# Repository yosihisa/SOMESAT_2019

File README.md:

# SOMESAT 種コン2019

## これはなに
SOMESAT種コン2019関係のプロジェクトを管理するリポジトリです。  
各CanSatの基板データとかプログラムとかいろいろ  
<br>
<font color="Red">注意: ESFF(仮称)はこのリポジトリではありません。</font>

## 編集するときは？  
自分のブランチを作ってそこにpushしてください。  
その後masterにプルリク送ってください。  
**masterを直接書き換えないでください。**   

## 何があるの？
ディレクトリ構成は以下の通り  

- PCB  
基板データ関係
    - EDAMAME_S  
    えだまめSの基板データ  
    n_yosihisa

    - EDAMAME_WiFimodule  
    ZUNDA～えだまめ!!に使われていたESP8266無線モジュールの基板データ  
    yuuitirou528  

    -  	EDAMAMEv2  
    画像認識機の基板データ  
    n_yosihisa  

- firmware  
プログラム関係  
    - EDAMAME_S  
    環境  
    ・ Arduino IDE  
    ・ ESP32  
    えだまめSのスケッチ  
    n_yosihisa

    - EDAMAME_WiFimodule  
    環境  
    ・ Arduino IDE  
    ・ ESP8266  
    ZUNDA～えだまめ!!に使われていたESP8266無線モジュールのスケッチ  
    yuuitirou528  

    -  EDAMAMEv2  
    環境  
    ・C(HAL)  
    ・Atollic TrueSTUDIO  
    ・CubeMX  
    ・STM32F446   
    画像認識機のプログラム  
    n_yosihisa  

- documents  
文書関係  
仕様書など  

### ファイルを書き替えるときの注意  
基本的に自分の担当しているもののディレクトの中身以外は変更しないように (2018/10/5)
***

## 著作権などについて
基本的に著作権は各作者に帰属します。  
種コンが終わるまで自分が書いたもの以外原則公開禁止です。  
ただし、種コン終了後、このリポジトリをpublicにする可能性があります。

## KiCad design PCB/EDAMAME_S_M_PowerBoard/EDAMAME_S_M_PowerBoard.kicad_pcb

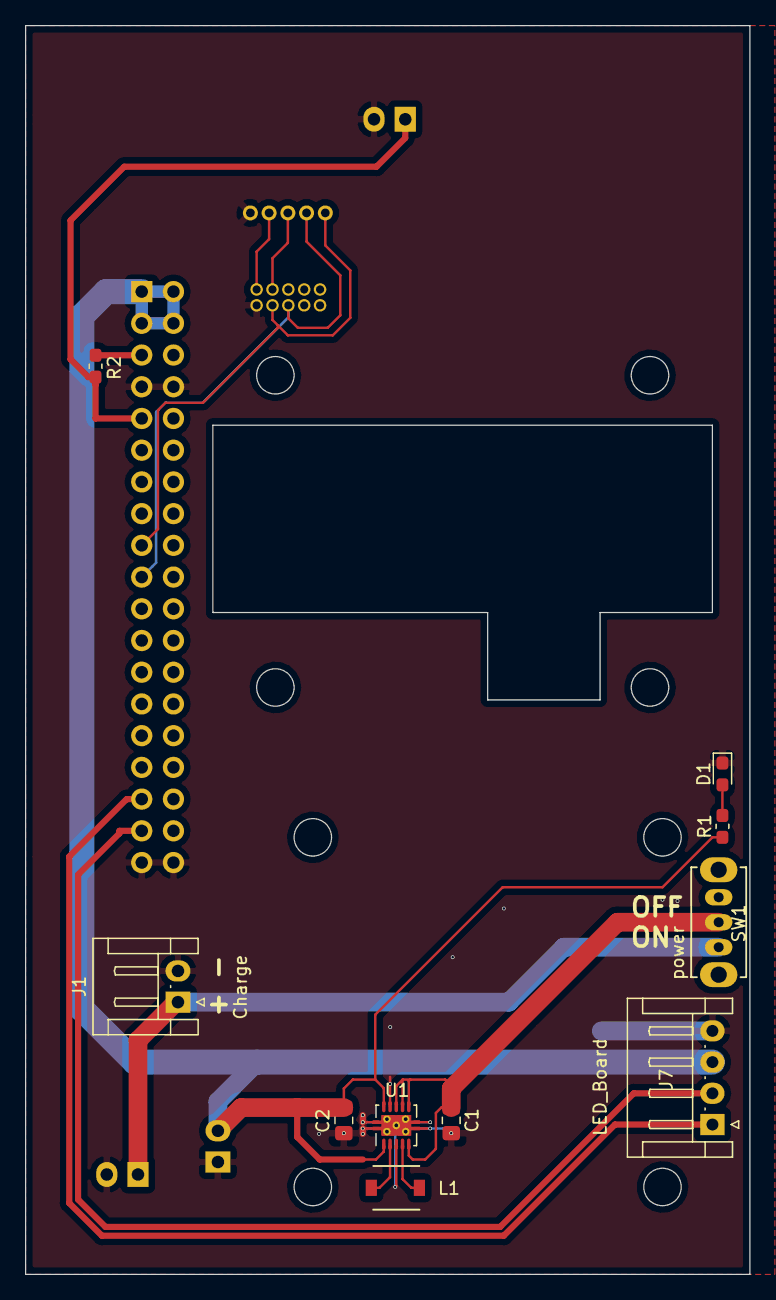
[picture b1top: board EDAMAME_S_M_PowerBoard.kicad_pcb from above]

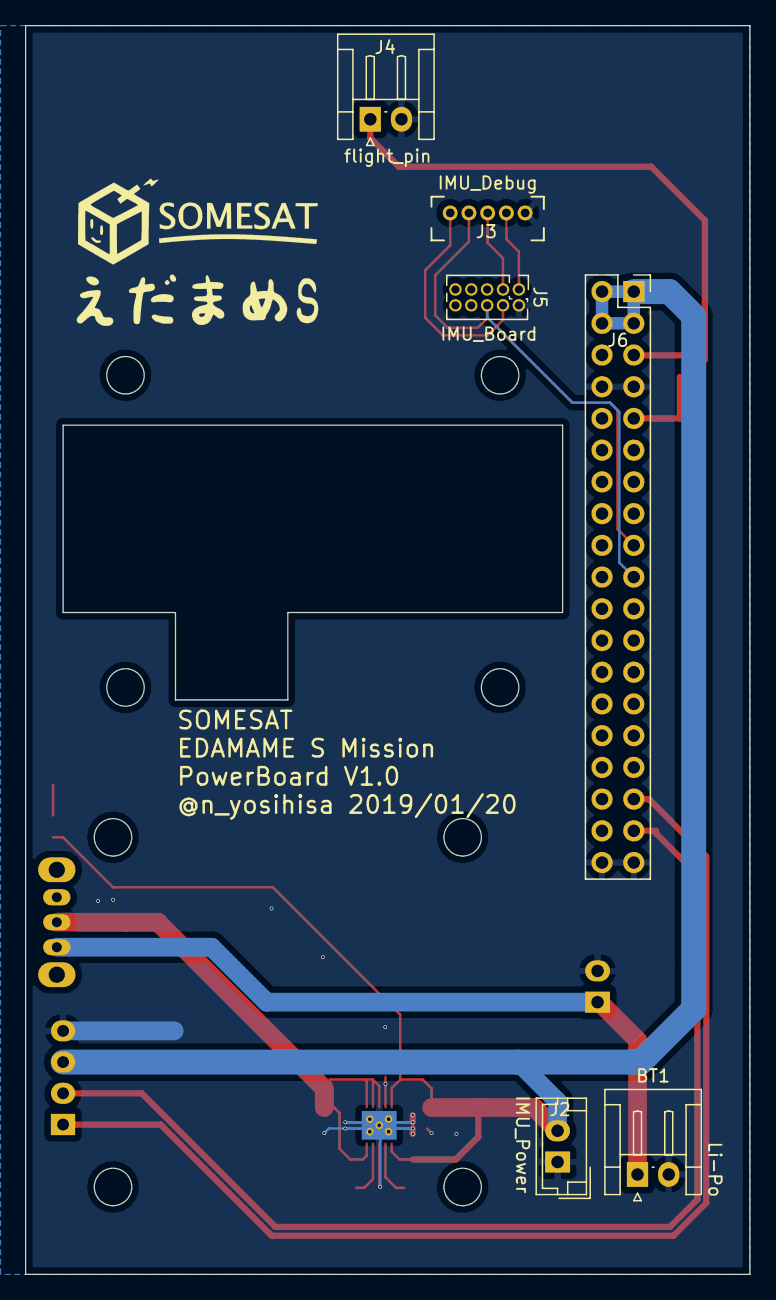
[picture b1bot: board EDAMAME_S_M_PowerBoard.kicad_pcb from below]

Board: 2 copper layers, 58.0 x 100.0 mm, 16 parts (6 on the bottom side), 15 nets.

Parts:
BT1: Li-Po; JST_EH_S02B-EH_1x02_P2.50mm_Horizontal
C1, C2: 10u; C_0805_2012Metric_Pad1.15x1.40mm_HandSolder
D1: LED_Small; LED_0603_1608Metric_Pad1.05x0.95mm_HandSolder
J1: Charge; JST_EH_S02B-EH_1x02_P2.50mm_Horizontal
J2: IMU_Power; JST_EH_B02B-EH-A_1x02_P2.50mm_Vertical
J3: IMU_Debug; STlink
J4: flight_pin; JST_EH_S02B-EH_1x02_P2.50mm_Horizontal
J5: IMU_Board; PinHeader_2x05_P1.27mm_Vertical
J6: OBC_Board; PinSocket_2x19_P2.54mm_Vertical
J7: LED_Board; JST_EH_S04B-EH_1x04_P2.50mm_Horizontal
L1: 2.2uH; inductor_VLF4012-2R2
R1, R2: R; R_0603_1608Metric_Pad1.05x0.95mm_HandSolder
SW1: power; SS-12D01-VG4
U1: TPS63002; Texas_S-PVSON-N10_ThermalVias

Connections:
+3V3: J6.5, R2.2
+5V: C2.1, J2.2, J6.1, J6.2, J6.3, J6.4, J7.3, R1.1, U1.1, U1.10
+BATT: C1.1, SW1.2, U1.5, U1.6, U1.7, U1.8
/IMU_RX: J3.2, J5.6, J6.19
/IMU_TX: J3.1, J5.4, J6.17
/SCL: J6.33, J7.1
/SDA: J6.35, J7.2
/SWCLK: J3.3, J5.3
/SWDIO: J3.4, J5.1
/flight_pin: J4.1, J6.9, R2.1
GND: BT1.2, C1.2, C2.2, D1.1, J1.2, J2.1, J3.5, J4.2, J5.2, J6.7, J6.8, J6.37, J6.38, J7.4, U1.3, U1.9, U1.11
unnamed: BT1.1, J1.1, SW1.1
unnamed: D1.2, R1.2
unnamed: L1.1, U1.4
unnamed: L1.2, U1.2

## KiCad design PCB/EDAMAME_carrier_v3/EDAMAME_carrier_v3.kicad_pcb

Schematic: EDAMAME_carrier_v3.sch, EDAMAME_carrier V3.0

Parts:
BT1, BT2: Li-Po; JST_EH_S02B-EH_1x02_P2.50mm_Horizontal
BZ1: Buzzer; CP_Radial_Tantal_D10.5mm_P5.00mm
C1, C2: 0.1u; C_0603_1608Metric_Pad1.05x0.95mm_HandSolder
C3: 10u; C_0805_2012Metric_Pad1.15x1.40mm_HandSolder
D1, D2, D3: LED_Small; LED_0603_1608Metric_Pad1.05x0.95mm_HandSolder
J1: Charge; JST_EH_B03B-EH-A_1x03_P2.50mm_Vertical
J2: Debug; STlink
J3: flightpin; JST_EH_S02B-EH_1x02_P2.50mm_Horizontal
J4: Nichrome1; JST_EH_S02B-EH_1x02_P2.50mm_Horizontal
J5: Nichrome2; JST_EH_S02B-EH_1x02_P2.50mm_Horizontal
J6: Nichrome3; JST_EH_S02B-EH_1x02_P2.50mm_Horizontal
J7: Nichrome4; JST_EH_S02B-EH_1x02_P2.50mm_Horizontal
Q1, Q2: NDS9936; SO-8_5.3x6.2mm_P1.27mm
R1, R2, R3, R4, R5, R6, R7: 1k; R_0603_1608Metric_Pad1.05x0.95mm_HandSolder
SW1: power; SS-12D01-VG4
SW2, SW3: Delay_0; DIP-10_W7.62mm_LongPads
U1: STM32F042F6Px; TSSOP-20_4.4x6.5mm_P0.65mm
U2: NJM2391DL1-33; TO-252-2

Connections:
+3V3: C1.1, C3.1, R1.1, R3.1, U1.5, U1.16, U2.3 (VO)
+BATT: C2.1, J4.2, J5.2, J6.2, J7.2, SW1.2, U2.1 (VI)
/Buzzer: R2.1, U1.14
/Delay0_0.5s: SW3.4, U1.9
/Delay0_0.25s: SW3.5, U1.10
/Delay0_1s: SW3.3, U1.8
/Delay0_2s: SW3.2, U1.7
/Delay0_4s: SW3.1, U1.6
/Delay1_0.5s: SW2.6, U1.11
/Delay1_1s: SW2.7, U1.12
/Delay1_2s: SW2.8, U1.13
/Delay2_0.5s: SW2.9, U1.3
/Delay2_1s: SW2.10, U1.2
/Flight_SW: J3.1, R3.2, U1.1
/PWM0: Q1.2, Q1.4, R4.1, R6.1, U1.17
/PWM1: Q2.2, Q2.4, R5.1, R7.1, U1.18
/SWCLK: J2.3, U1.19
/SWDIO: J2.4, U1.20
GND: BT2.2, BZ1.2, C1.2, C2.2, C3.2, D1.1, D2.1, D3.1, J1.3, J2.5, J3.2, Q1.1, Q1.3, Q2.1, Q2.3, R6.2, R7.2, SW2.1, SW2.2, SW2.3, SW2.4, SW2.5, SW3.6, SW3.7, SW3.8, SW3.9, SW3.10, U1.15, U2.2 (GND)
unnamed: BT1.1, J1.1, SW1.1
unnamed: BT1.2, BT2.1, J1.2
unnamed: BZ1.1, R2.2
unnamed: D1.2, R1.2
unnamed: D2.2, R4.2
unnamed: D3.2, R5.2
unnamed: J4.1, Q1.7, Q1.8
unnamed: J5.1, Q1.5, Q1.6
unnamed: J6.1, Q2.7, Q2.8
unnamed: J7.1, Q2.5, Q2.6

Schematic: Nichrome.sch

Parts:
D101, D102, D103, D104: LED_Small; LED_0603_1608Metric_Pad1.05x0.95mm_HandSolder
J101: Nichrome1; JST_EH_S02B-EH_1x02_P2.50mm_Horizontal
J102: Nichrome2; JST_EH_S02B-EH_1x02_P2.50mm_Horizontal
J103: Nichrome3; JST_EH_S02B-EH_1x02_P2.50mm_Horizontal
J104: Nichrome4; JST_EH_S02B-EH_1x02_P2.50mm_Horizontal
R101, R102, R103, R104: 1k; R_0603_1608Metric_Pad1.05x0.95mm_HandSolder
T101: Nichrome1; TerminalBlock_MetzConnect_Type101_RT01602HBWC_1x02_P5.08mm_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
T102: Nichrome2; TerminalBlock_MetzConnect_Type101_RT01602HBWC_1x02_P5.08mm_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
T103: Nichrome3; TerminalBlock_MetzConnect_Type101_RT01602HBWC_1x02_P5.08mm_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
T104: Nichrome4; TerminalBlock_MetzConnect_Type101_RT01602HBWC_1x02_P5.08mm_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

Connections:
unnamed: D101.1, R101.2
unnamed: D101.2, J101.1, T101.1
unnamed: D102.1, R102.2
unnamed: D102.2, J102.1, T102.1
unnamed: D103.1, R103.2
unnamed: D103.2, J103.1, T103.1
unnamed: D104.1, R104.2
unnamed: D104.2, J104.1, T104.1
unnamed: J101.2, R101.1, T101.2
unnamed: J102.2, R102.1, T102.2
unnamed: J103.2, R103.1, T103.2
unnamed: J104.2, R104.1, T104.2

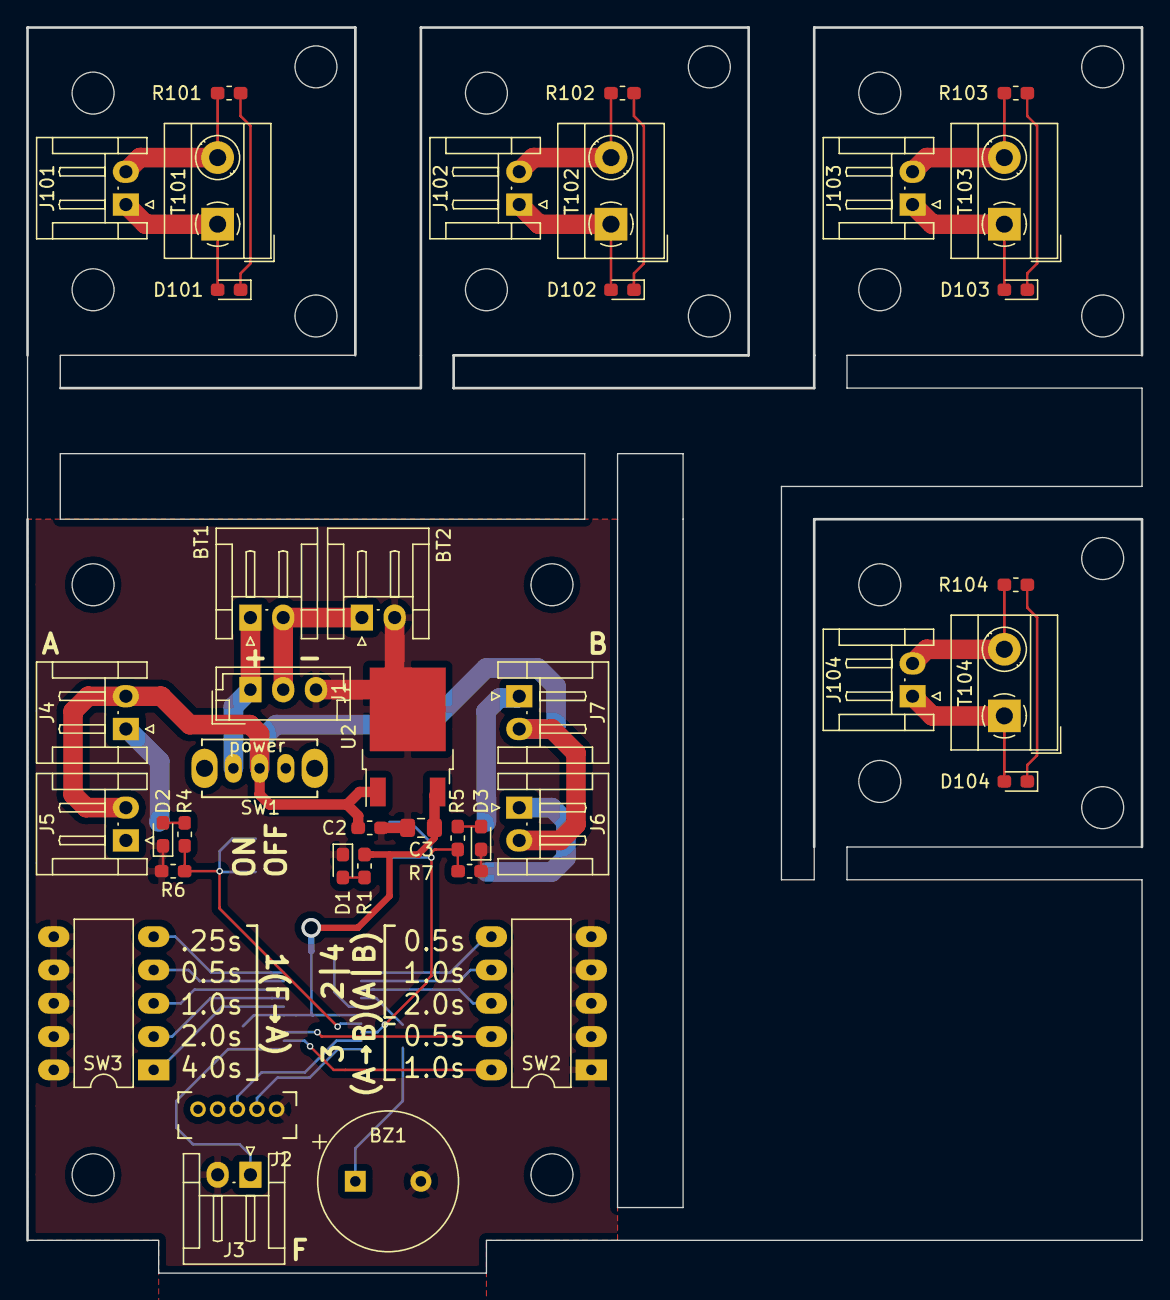
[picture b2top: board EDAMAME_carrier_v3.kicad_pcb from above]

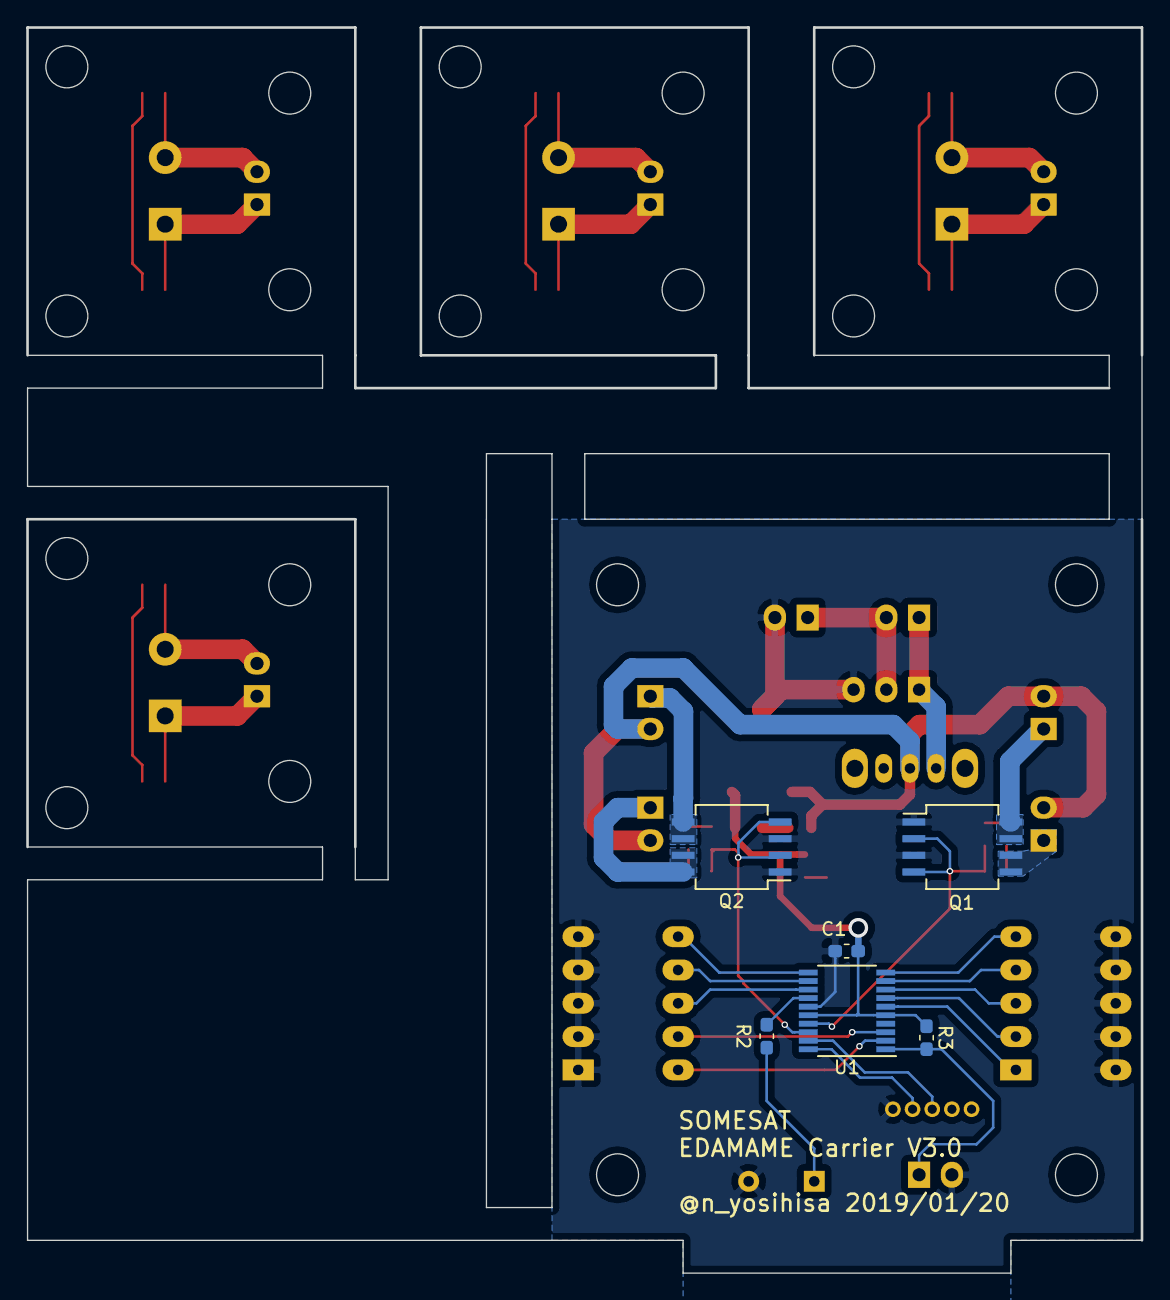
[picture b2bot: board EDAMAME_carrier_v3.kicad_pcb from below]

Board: 2 copper layers, 85.0 x 95.0 mm, 46 parts (6 on the bottom side), 41 nets.

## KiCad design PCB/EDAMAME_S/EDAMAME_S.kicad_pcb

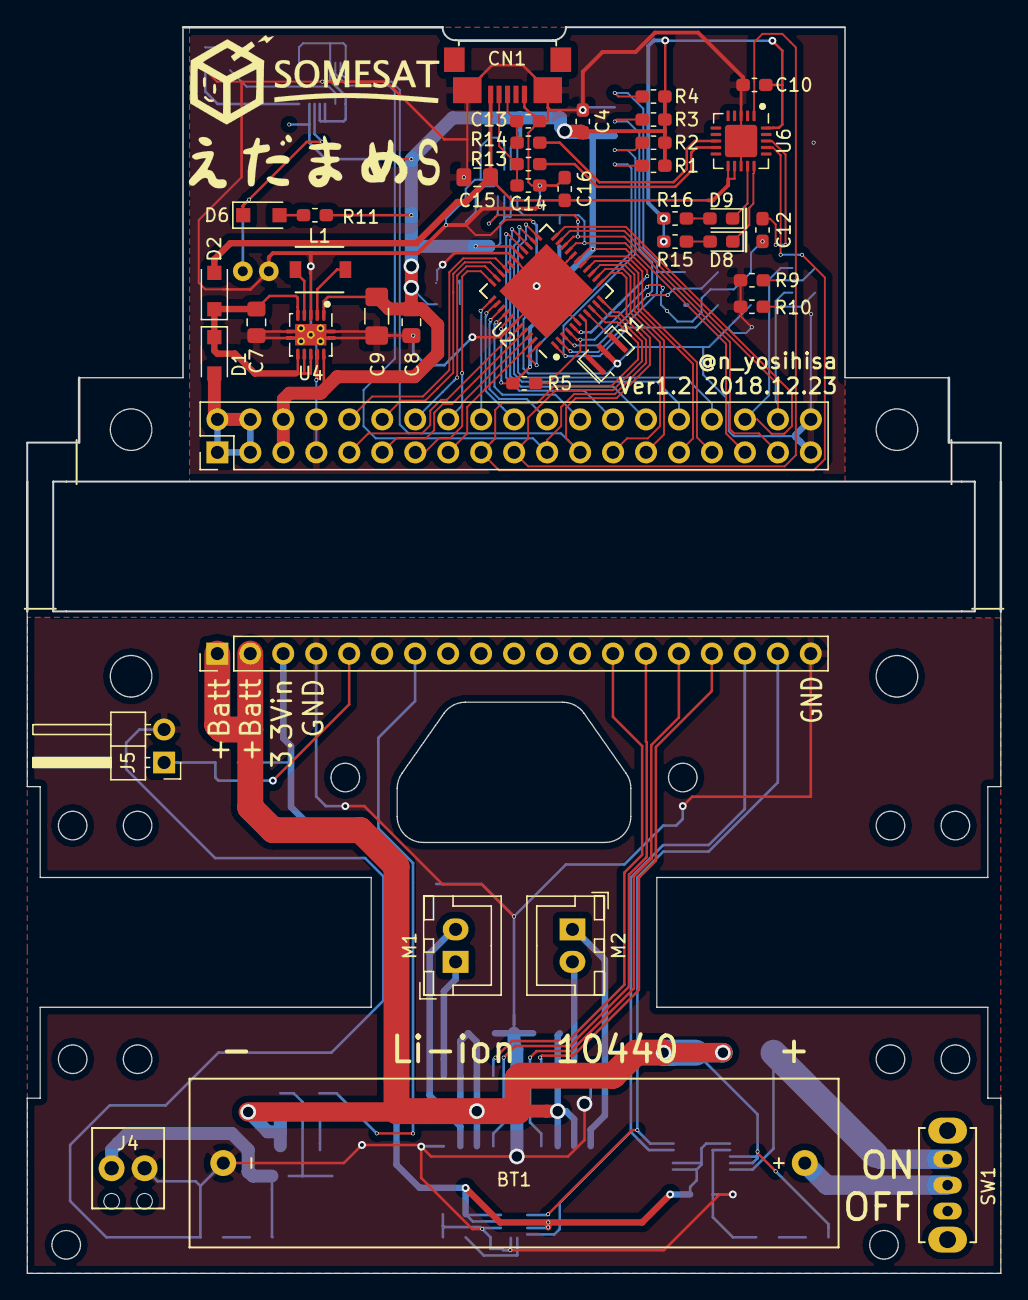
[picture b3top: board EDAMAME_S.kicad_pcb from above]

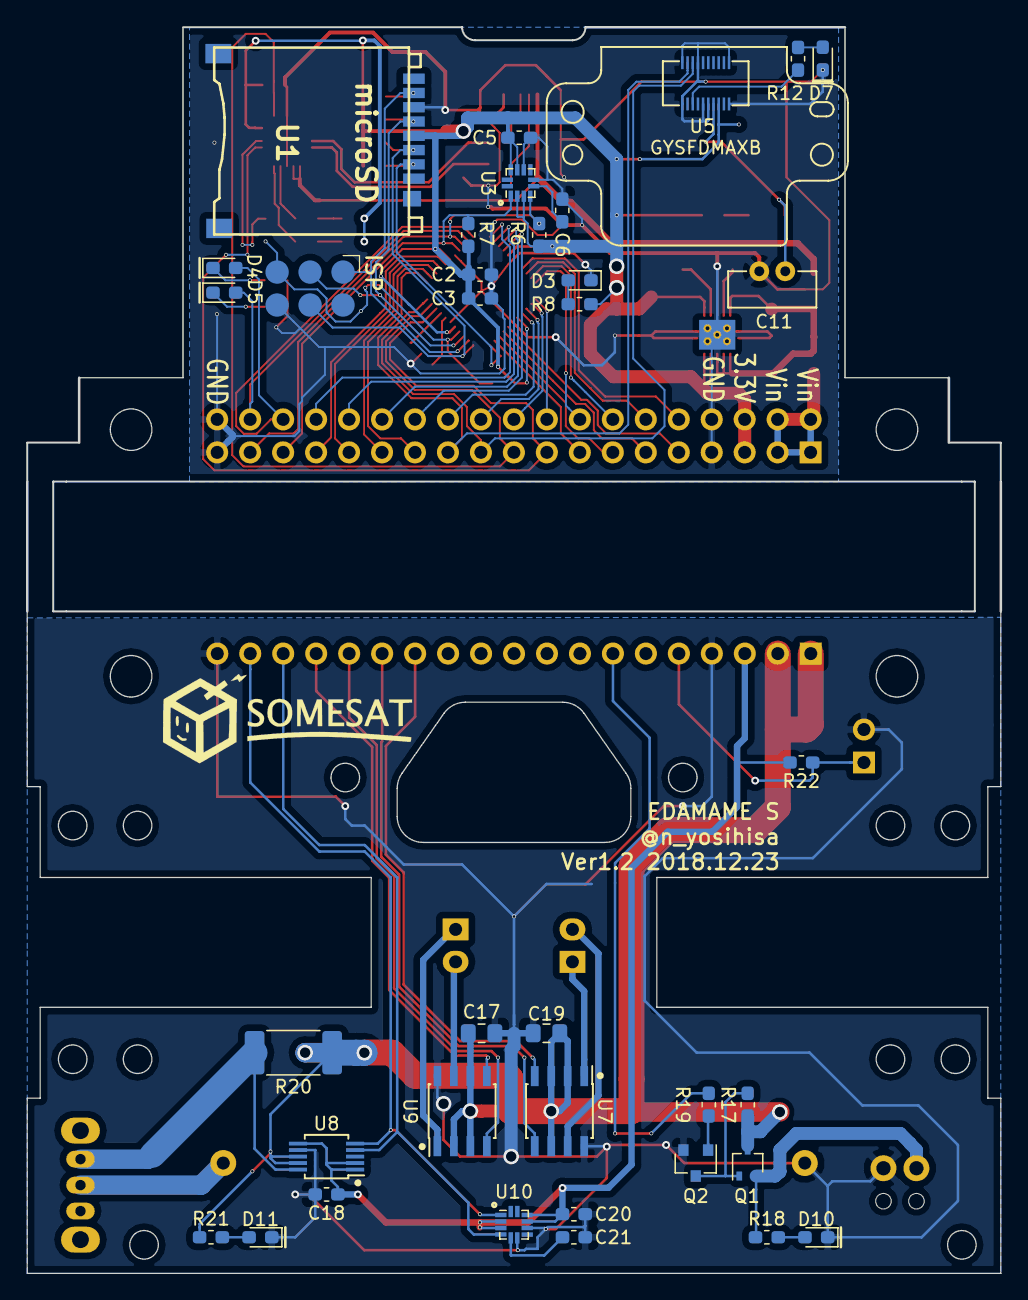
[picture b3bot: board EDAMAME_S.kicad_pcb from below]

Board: 2 copper layers, 75.0 x 96.0 mm, 77 parts (35 on the bottom side), 82 nets.

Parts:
BT1: 10440; BH-411
C2, C3, C4, C5, C6, C10, C12, C16, C18, C20, C21: 0.1u; C_0603_1608Metric_Pad1.05x0.95mm_HandSolder
C7, C8, C15, C17, C19: 10u; C_0805_2012Metric_Pad1.15x1.40mm_HandSolder
C9: 100u; C_1206_3216Metric_Pad1.42x1.75mm_HandSolder
C11: 0.22F 3.3V; MS621FE_FL11E
C13, C14: 47p; C_0603_1608Metric_Pad1.05x0.95mm_HandSolder
CN1: USB-B-MICRO; Micro-USB
D1, D2, D6: GS1010FL; D_SOD-123F
D3, D11: POWER; LED_0603_1608Metric_Pad1.05x0.95mm_HandSolder
D4: LED1; LED_0603_1608Metric_Pad1.05x0.95mm_HandSolder
D5: LED2; LED_0603_1608Metric_Pad1.05x0.95mm_HandSolder
D7: 1PPS; LED_0603_1608Metric_Pad1.05x0.95mm_HandSolder
D8: TX_LED; LED_0603_1608Metric_Pad1.05x0.95mm_HandSolder
D9: RX_LED; LED_0603_1608Metric_Pad1.05x0.95mm_HandSolder
D10: Nichrome; LED_0603_1608Metric_Pad1.05x0.95mm_HandSolder
J1: Conn; PinHeader_2x19_P2.54mm_Vertical
J2: ISP; AVR_ISP
J3: Conn; PinHeader_1x19_P2.54mm_Vertical
J4: Nichrome; MPT0.5_2-2.54
J5: FlightPin; PinHeader_1x02_P2.54mm_Horizontal
L1: 2.2uH; inductor_VLF4012-2R2
M1: Motor_L; JST_XH_B02B-XH-A_1x02_P2.50mm_Vertical
M2: Motor_R; JST_XH_B02B-XH-A_1x02_P2.50mm_Vertical
Q1: MTM231102LBF; SOT-323_SC-70
Q2: 2SC2712; SOT-23
R1, R2, R3, R4, R5: 10k; R_0603_1608Metric_Pad1.05x0.95mm_HandSolder
R6, R7: 2.2k; R_0603_1608Metric_Pad1.05x0.95mm_HandSolder
R8, R9, R10, R12, R15, R16: 1k; R_0603_1608Metric_Pad1.05x0.95mm_HandSolder
R11: 100; R_0603_1608Metric_Pad1.05x0.95mm_HandSolder
R13, R14: 33; R_0603_1608Metric_Pad1.05x0.95mm_HandSolder
R17, R19, R22: 10K; R_0603_1608Metric_Pad1.05x0.95mm_HandSolder
R18, R21: 1K; R_0603_1608Metric_Pad1.05x0.95mm_HandSolder
R20: 10m; R_2512_6332Metric_Pad1.52x3.35mm_HandSolder
SW1: power; SS-12D01-VG4
U1: microSD
U2: ATMEGA1284P-MU; QFN-44-1EP_7x7mm_P0.5mm_EP5.15x5.15mm
U3, U10: LSM303C; LGA-12_2x2mm_P0.5mm_HandSolder
U4: TPS63001; Texas_S-PVSON-N10_ThermalVias
U5: GYSFDMAXB
U6: FT231XQ; QFN-20-1EP_4x4mm_P0.5mm_EP2.5x2.5mm
U7, U9: BD6211F; SOIC-8_3.9x4.9mm_P1.27mm
U8: INA226; MSOP-10_3x3mm_P0.5mm
Y1: 16MHz; Resonator_SMD_muRata_CSTxExxV-3Pin_3.0x1.1mm

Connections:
+3V3: C2.1, C3.1, C4.1, C5.1, C8.1, C9.1, C10.1, J1.5, J1.6, R1.2, R2.2, R3.2, R4.2, R5.1, R6.1, R7.1, R8.2, R11.1, R15.1, R16.1, U1.4, U2.5, U2.17, U2.27, U2.38, U3.2, U3.3, U3.9, U3.10, U4.1, U4.10, U5.16, U6.20
+5V: C15.1, C16.1, CN1.1, D2.2, U6.11, U6.12
+BATT: C17.1, C19.1, J3.1, J3.2, Q1.3, R17.2, R20.1, R21.1, U7.2, U7.3, U7.6, U8.8, U8.9, U9.2, U9.3, U9.6
/EDAMAME_S_Ex/FlightPin: J3.5, J5.1, R22.1
/EDAMAME_S_Ex/MOTOR_LF: J3.13, U7.4
/EDAMAME_S_Ex/MOTOR_LR: J3.14, U7.5
/EDAMAME_S_Ex/MOTOR_RF: J3.16, U9.5
/EDAMAME_S_Ex/MOTOR_RR: J3.15, U9.4
/EDAMAME_S_Ex/Nichrome: J3.7, R19.2
/EDAMAME_S_Ex/SCL: J3.18, U8.5, U10.1
/EDAMAME_S_Ex/SDA: J3.17, U8.4, U10.4
/EDAMAME_S_core/0: J1.9, U2.40
/EDAMAME_S_core/1: J1.11, U2.41
/EDAMAME_S_core/2: J1.13, U2.42
/EDAMAME_S_core/3-: J1.15, U2.43
/EDAMAME_S_core/12-: J1.25, U2.13
/EDAMAME_S_core/13-: J1.27, U2.14
/EDAMAME_S_core/14-: J1.29, U2.15
/EDAMAME_S_core/15-: J1.31, U2.16
/EDAMAME_S_core/18: D5.2, J1.36, U2.21
/EDAMAME_S_core/19: D4.2, J1.34, U2.22
/EDAMAME_S_core/20: J1.32, U2.23
/EDAMAME_S_core/21: J1.30, U2.24
/EDAMAME_S_core/22: J1.28, U2.25
/EDAMAME_S_core/23: J1.26, U2.26
/EDAMAME_S_core/A0: J1.24, U2.37
/EDAMAME_S_core/A1: J1.22, U2.36
/EDAMAME_S_core/A2: J1.20, U2.35
/EDAMAME_S_core/A3: J1.18, U2.34
/EDAMAME_S_core/A4: J1.16, U2.33
/EDAMAME_S_core/A5: J1.14, U2.32
/EDAMAME_S_core/A6: J1.12, U2.31
/EDAMAME_S_core/A7: J1.10, U2.30
/EDAMAME_S_core/AVR→GPS: J1.23, U2.12, U5.3
/EDAMAME_S_core/AVR→PC: J1.19, U2.10, U6.1
/EDAMAME_S_core/GPS→AVR: J1.21, U2.11, U5.5
/EDAMAME_S_core/I2C_SCL: J1.33, R7.2, U2.19, U3.1
/EDAMAME_S_core/I2C_SDA: J1.35, R6.2, U2.20, U3.4
/EDAMAME_S_core/MISO: J2.1, R4.1, U1.7, U2.2
/EDAMAME_S_core/MOSI: J2.4, R2.1, U1.3, U2.1
/EDAMAME_S_core/PC→AVR: J1.17, U2.9, U6.17
/EDAMAME_S_core/RST: C12.2, J2.5, R5.2, U2.4
/EDAMAME_S_core/SCK: J2.3, R3.1, U1.5, U2.3
/EDAMAME_S_core/SS: R1.1, U1.2, U2.44
GND: C2.2, C3.2, C4.2, C5.2, C6.2, C7.2, C8.2, C9.2, C10.2, C11.2, C13.2, C14.2, C15.2, C16.2, CN1.5, CN1.6, CN1.7, D3.1, D7.1, J1.7, J1.8, J1.37, J1.38, J2.6, R9.2, R10.2, U1.6, U2.6, U2.18, U2.28, U2.39, U2.45, U3.6, U3.8, U4.3, U4.9, U4.11, U5.1, U5.2, U5.7, U5.10, U5.12, U5.19, U5.20, U6.3, U6.13, U6.21, Y1.2
GNDPWR: BT1.2, C17.2, C18.2, C19.2, C20.2, C21.2, D10.1, D11.1, J3.4, J3.19, J4.2, J5.2, Q2.2, U7.8, U8.7, U9.8, U10.6, U10.8
unnamed: BT1.1, SW1.2
unnamed: C6.1, U3.5
unnamed: C7.1, D1.1, D2.1, U4.5, U4.6, U4.7, U4.8
unnamed: C11.1, D6.1, U5.14
unnamed: C12.1, U6.18
unnamed: C13.1, CN1.3, R14.2
unnamed: C14.1, CN1.2, R13.2
unnamed: C21.1, U10.5
unnamed: D1.2, J1.1, J1.2, J1.3, J1.4
unnamed: D3.2, R8.1
unnamed: D4.1, R9.1
unnamed: D5.1, R10.1
unnamed: D6.2, R11.2
unnamed: D7.2, R12.1
unnamed: D8.1, U6.15
unnamed: D8.2, R15.2
unnamed: D9.1, U6.14
unnamed: D9.2, R16.2
unnamed: D10.2, R18.2
unnamed: D11.2, R21.2
unnamed: J4.1, Q1.2, R18.1
unnamed: L1.1, U4.4
unnamed: L1.2, U4.2
unnamed: M1.1, U7.1
unnamed: M1.2, U7.7
unnamed: M2.1, U9.1
unnamed: M2.2, U9.7
unnamed: Q1.1, Q2.3, R17.1
unnamed: Q2.1, R19.1
unnamed: R12.2, U5.6
unnamed: R13.1, U6.9
unnamed: R14.1, U6.8
unnamed: R20.2, SW1.1, U8.10
unnamed: U2.7, Y1.1
unnamed: U2.8, Y1.3
VCC: C18.1, C20.1, J3.3, R22.2, U8.1, U8.2, U8.6, U10.2, U10.3, U10.9, U10.10

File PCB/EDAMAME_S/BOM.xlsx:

リファレンス | 定数テイスウ | フットプリント | データシート | 品番ヒンバン | 購入先コウニュウサキ | Qty | 備考ビコウ
BT1 | 10440 | user:BH-411 |  | P-02670 | 秋月 | 1 | 単四電池BOXを流用タンヨンデンチリュウヨウ |  | メモ
C2 | 0.1u | Capacitor_SMD:C_0603_1608Metric_Pad1.05x0.95mm_HandSolder | ~ |  |  | 1 |  |  | 電圧指定の無いコンデンサは5V耐圧以上のものを使用デンアツシテイナタイアツイジョウシヨウ
C3 | 0.1u | Capacitor_SMD:C_0603_1608Metric_Pad1.05x0.95mm_HandSolder | ~ |  |  | 1
C4 | 0.1u | Capacitor_SMD:C_0603_1608Metric_Pad1.05x0.95mm_HandSolder | ~ |  |  | 1
C5 | 0.1u | Capacitor_SMD:C_0603_1608Metric_Pad1.05x0.95mm_HandSolder | ~ |  |  | 1 | C5とC20も同様に排他的 どちらか1つのみ実装するが両方実装してもよいドウヨウハイタテキジッソウリョウホウジッソウ
C6 | 0.1u | Capacitor_SMD:C_0603_1608Metric_Pad1.05x0.95mm_HandSolder | ~ |  |  | 1 | C6とC21も同様に排他的 どちらか1つのみ実装するが両方実装してもよいドウヨウハイタテキジッソウリョウホウジッソウ
C7 | 10u | Capacitor_SMD:C_0805_2012Metric_Pad1.15x1.40mm_HandSolder | ~ |  |  | 1
C8 | 10u | Capacitor_SMD:C_0805_2012Metric_Pad1.15x1.40mm_HandSolder | ~ |  |  | 1
C9 | 100u | Capacitor_SMD:C_1206_3216Metric_Pad1.42x1.75mm_HandSolder | ~ |  |  | 1
C10 | 0.1u | Capacitor_SMD:C_0603_1608Metric_Pad1.05x0.95mm_HandSolder | ~ |  |  | 1
C11 | 0.22F 3.3V | user:MS621FE_FL11E | ~ | P-00240 | 秋月 | 1
C12 | 0.1u | Capacitor_SMD:C_0603_1608Metric_Pad1.05x0.95mm_HandSolder | ~ |  |  | 1
C13 | 47p | Capacitor_SMD:C_0603_1608Metric_Pad1.05x0.95mm_HandSolder | ~ |  |  | 1
C14 | 47p | Capacitor_SMD:C_0603_1608Metric_Pad1.05x0.95mm_HandSolder | ~ |  |  | 1
C15 | 10u | Capacitor_SMD:C_0805_2012Metric_Pad1.15x1.40mm_HandSolder | ~ |  |  | 1
C16 | 0.1u | Capacitor_SMD:C_0603_1608Metric_Pad1.05x0.95mm_HandSolder | ~ |  |  | 1
C17 | 10u | Capacitor_SMD:C_0805_2012Metric_Pad1.15x1.40mm_HandSolder |  |  |  | 1
C18 | 0.1u | Capacitor_SMD:C_0603_1608Metric_Pad1.05x0.95mm_HandSolder |  |  |  | 1
C19 | 10u | Capacitor_SMD:C_0805_2012Metric_Pad1.15x1.40mm_HandSolder |  |  |  | 1
C20 | 0.1u | Capacitor_SMD:C_0603_1608Metric_Pad1.05x0.95mm_HandSolder | ~ |  |  | 1 | C5とC20も同様に排他的 どちらか1つのみ実装するが両方実装してもよいドウヨウハイタテキジッソウリョウホウジッソウ
C21 | 0.1u | Capacitor_SMD:C_0603_1608Metric_Pad1.05x0.95mm_HandSolder | ~ |  |  | 1 | C6とC21も同様に排他的 どちらか1つのみ実装するが両方実装してもよいドウヨウハイタテキジッソウリョウホウジッソウ
CN1 | USB-B-MICRO | user:Micro-USB | http://akizukidenshi.com/download/ds/hirose/ZX62R-B-5P.pdf | C-05254 | 秋月 | 1
D1 | GS1010FL | Diode_SMD:D_SOD-123F | http://akizukidenshi.com/download/ds/panjit/GS1000FL_SERIES.pdf | I-06014 | 秋月 | 1
D2 | GS1010FL | Diode_SMD:D_SOD-123F | http://akizukidenshi.com/download/ds/panjit/GS1000FL_SERIES.pdf | I-06014 | 秋月 | 1
D3 | POWER | LED_SMD:LED_0603_1608Metric_Pad1.05x0.95mm_HandSolder | ~ |  |  | 1
D4 | LED1 | LED_SMD:LED_0603_1608Metric_Pad1.05x0.95mm_HandSolder | ~ |  |  | 1
D5 | LED2 | LED_SMD:LED_0603_1608Metric_Pad1.05x0.95mm_HandSolder | ~ |  |  | 1
D6 | GS1010FL | Diode_SMD:D_SOD-123F | http://akizukidenshi.com/download/ds/panjit/GS1000FL_SERIES.pdf | I-06014 | 秋月 | 1
D7 | 1PPS | LED_SMD:LED_0603_1608Metric_Pad1.05x0.95mm_HandSolder | ~ |  |  | 1
D8 | TX_LED | LED_SMD:LED_0603_1608Metric_Pad1.05x0.95mm_HandSolder | ~ |  |  | 1
D9 | RX_LED | LED_SMD:LED_0603_1608Metric_Pad1.05x0.95mm_HandSolder | ~ |  |  | 1
D10 | Nichrome | LED_SMD:LED_0603_1608Metric_Pad1.05x0.95mm_HandSolder |  |  |  | 1
D11 | POWER | LED_SMD:LED_0603_1608Metric_Pad1.05x0.95mm_HandSolder |  |  |  | 1
J1 | Conn | Connector_PinHeader_2.54mm:PinHeader_2x19_P2.54mm_Vertical | ~ |  |  | 1 | 2.54mmピッチ 2x19 ピンソケット
J2 | ISP | user:AVR_ISP | ~ |  |  | 1 | AVRマイコン書込み用カキコヨウ
J3 | Conn | Connector_PinHeader_2.54mm:PinHeader_1x19_P2.54mm_Vertical | ~ |  |  | 1 | 2.54mmピッチ 1x19 ピンヘッダ
J4 | Nichrome | user:MPT0.5_2-2.54 | http://akizukidenshi.com/catalog/g/gP-08450/ | P-08450 | 秋月 | 1
J5 | FlightPin | Connector_PinHeader_2.54mm:PinHeader_1x02_P2.54mm_Horizontal |  |  |  | 1
L1 | 2.2uH | user:inductor_VLF4012-2R2 | ~ | 644-1952 | RS | 1
M1 | Motor_L | Connector_JST:JST_XH_B02B-XH-A_1x02_P2.50mm_Vertical |  |  |  | 1
M2 | Motor_R | Connector_JST:JST_XH_B02B-XH-A_1x02_P2.50mm_Vertical |  |  |  | 1
Q1 | MTM231102LBF | Package_TO_SOT_SMD:SOT-323_SC-70 | ~ | 787-7526 | RS | 1
Q2 | 2SC2712 | Package_TO_SOT_SMD:SOT-23 |  | I-00761 | 秋月 | 1
R1 | 10k | Resistor_SMD:R_0603_1608Metric_Pad1.05x0.95mm_HandSolder | ~ |  |  | 1
R2 | 10k | Resistor_SMD:R_0603_1608Metric_Pad1.05x0.95mm_HandSolder | ~ |  |  | 1
R3 | 10k | Resistor_SMD:R_0603_1608Metric_Pad1.05x0.95mm_HandSolder | ~ |  |  | 1
R4 | 10k | Resistor_SMD:R_0603_1608Metric_Pad1.05x0.95mm_HandSolder | ~ |  |  | 1
R5 | 10k | Resistor_SMD:R_0603_1608Metric_Pad1.05x0.95mm_HandSolder | ~ |  |  | 1
R6 | 2.2k | Resistor_SMD:R_0603_1608Metric_Pad1.05x0.95mm_HandSolder | ~ |  |  | 1
R7 | 2.2k | Resistor_SMD:R_0603_1608Metric_Pad1.05x0.95mm_HandSolder | ~ |  |  | 1
R8 | 1k | Resistor_SMD:R_0603_1608Metric_Pad1.05x0.95mm_HandSolder | ~ |  |  | 1
R9 | 1k | Resistor_SMD:R_0603_1608Metric_Pad1.05x0.95mm_HandSolder | ~ |  |  | 1
R10 | 1k | Resistor_SMD:R_0603_1608Metric_Pad1.05x0.95mm_HandSolder | ~ |  |  | 1
R11 | 100 | Resistor_SMD:R_0603_1608Metric_Pad1.05x0.95mm_HandSolder | ~ |  |  | 1
R12 | 1k | Resistor_SMD:R_0603_1608Metric_Pad1.05x0.95mm_HandSolder | ~ |  |  | 1
R13 | 33 | Resistor_SMD:R_0603_1608Metric_Pad1.05x0.95mm_HandSolder | ~ |  |  | 1
R14 | 33 | Resistor_SMD:R_0603_1608Metric_Pad1.05x0.95mm_HandSolder | ~ |  |  | 1
R15 | 1k | Resistor_SMD:R_0603_1608Metric_Pad1.05x0.95mm_HandSolder | ~ |  |  | 1
R16 | 1k | Resistor_SMD:R_0603_1608Metric_Pad1.05x0.95mm_HandSolder | ~ |  |  | 1
R17 | 10K | Resistor_SMD:R_0603_1608Metric_Pad1.05x0.95mm_HandSolder |  |  |  | 1
R18 | 1K | Resistor_SMD:R_0603_1608Metric_Pad1.05x0.95mm_HandSolder |  |  |  | 1
R19 | 10K | Resistor_SMD:R_0603_1608Metric_Pad1.05x0.95mm_HandSolder |  |  |  | 1
R20 | 10m | Resistor_SMD:R_2512_6332Metric_Pad1.52x3.35mm_HandSolder |  | P-01886 | 秋月 | 1
R21 | 1K | Resistor_SMD:R_0603_1608Metric_Pad1.05x0.95mm_HandSolder |  |  |  | 1
SW1 | power | user:SS-12D01-VG4 |  | P-08791 | 秋月 | 1
U1 | microSD | user:microSD |  | C-02395 | 秋月 | 1
U2 | ATMEGA1284P-MU | Package_DFN_QFN:QFN-44-1EP_7x7mm_P0.5mm_EP5.15x5.15mm | https://avr.jp/user/DS/PDF/mega1284P.pdf | 127-8233 | RS | 1
U3 | LSM303C | user:LGA-12_2x2mm_P0.5mm_HandSolder | www.st.com/resource/en/datasheet/lsm303c.pdf | 110-6551 | RS | 1 | U3とU10は排他的 どちらか1つのみを実装するハイタテキジッソウ
U4 | TPS63001 | Package_SON:Texas_S-PVSON-N10_ThermalVias | http://www.tij.co.jp/jp/lit/ds/symlink/tps63001.pdf | 661-7067 | RS | 1
U5 | GYSFDMAXB | user:GYSFDMAXB |  | 772-6718 | RS | 1 | 品番はコネクタのみ モジュール本体は秋月のM-09990ヒンバンホンタイアキヅキ
U6 | FT231XQ | Package_DFN_QFN:QFN-20-1EP_4x4mm_P0.5mm_EP2.5x2.5mm | http://www.ftdichip.com/Products/ICs/FT231X.html | 757-0045 | RS | 1
U7 | BD6211F | Package_SO:SOIC-8_3.9x4.9mm_P1.27mm | http://akizukidenshi.com/download/ds/rohm/bd621x-j.pdf | I-05087 | 秋月 | 1
U8 | INA226 | Package_SO:MSOP-10_3x3mm_P0.5mm |  | 742-2889 | RS | 1
U9 | BD6211F | Package_SO:SOIC-8_3.9x4.9mm_P1.27mm | http://akizukidenshi.com/download/ds/rohm/bd621x-j.pdf | I-05087 | 秋月 | 1
U10 | LSM303C | user:LGA-12_2x2mm_P0.5mm_HandSolder | www.st.com/resource/en/datasheet/lsm303c.pdf | 110-6551 | RS | 1 | U3とU10は排他的 どちらか1つのみを実装するハイタテキジッソウ
Y1 | 16MHz | Crystal:Resonator_SMD_muRata_CSTxExxV-3Pin_3.0x1.1mm | ~ | 624-1077 | RS | 1

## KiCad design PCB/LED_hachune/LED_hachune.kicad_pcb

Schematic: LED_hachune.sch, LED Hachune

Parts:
C1: 100u; C_1210_3225Metric_Pad1.42x2.65mm_HandSolder
C2: 0.1u; C_0603_1608Metric_Pad1.05x0.95mm_HandSolder
C3, C4: 10u; C_0805_2012Metric_Pad1.15x1.40mm_HandSolder
D1, D2, D3, D4, D5: SLC-F11DDA-T1
D6: LED; LED_0603_1608Metric_Pad1.05x0.95mm_HandSolder
J1: POWER; JST_EH_S02B-EH_1x02_P2.50mm_Horizontal
J2: DATA; JST_EH_S03B-EH_1x03_P2.50mm_Horizontal
J3: STlink
JP1: EN; SolderJumper-2_P1.3mm_Open_Pad1.0x1.5mm
L1: 2.2uH VLF4012-2R2; inductor_VLF4012-2R2
R1, R2, R3, R4, R5, R6: R; R_0603_1608Metric_Pad1.05x0.95mm_HandSolder
U1, U4: M63806KP; SSOP-20_4.4x6.5mm_P0.65mm
U2: TPS63001; Texas_S-PVSON-N10_ThermalVias
U3: STM32F042K6Tx; LQFP-32_7x7mm_P0.8mm

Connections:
+3V3: C1.1, C2.1, C4.1, D1.1, D1.5, D2.1, D2.5, D3.1, D3.5, D4.1, D4.5, D5.1, D5.5, R1.1, R2.1, R3.1, R4.1, R5.1, R6.1, U2.1, U2.10, U3.1 (VDD), U3.5 (VDDA), U3.17 (VDDIO2)
+BATT: C3.1, J1.1, JP1.1, U2.5, U2.7, U2.8
/NRST: U3.4 (NRST)
/PWM_1B: U1.4, U3.8 (PA2)
/PWM_1G: U1.3, U3.7 (PA1)
/PWM_1R: U1.2, U3.6 (PA0)
/PWM_2B: U1.7, U3.13 (PA7)
/PWM_2G: U1.6, U3.12 (PA6)
/PWM_2R: U1.5, U3.9 (PA3)
/PWM_3B: U3.18 (PA8), U4.2
/PWM_3G: U1.9, U3.15 (PB1)
/PWM_3R: U1.8, U3.14 (PB0)
/PWM_4B: U3.21 (PA11), U4.5
/PWM_4G: U3.20 (PA10), U4.4, U4.7, U4.8
/PWM_4R: U3.19 (PA9), U4.3, U4.6
/PWM_LED: U3.10 (PA4), U4.9
/RX: J3.2
/Rx: U3.30 (PB7)
/SCL: J2.1, U3.3 (PF1)
/SDA: J2.2, U3.2 (PF0)
/SWCLK: J3.3, U3.24 (PA14)
/SWDIO: J3.4, U3.23 (PA13)
/TX: J3.1
/Tx: U3.29 (PB6)
GND: C1.2, C2.2, C3.2, C4.2, J1.2, J2.3, J3.5, U1.10, U2.3, U2.9, U3.16 (VSS), U3.32 (VSSA), U4.10
unnamed: D1.2, U1.19
unnamed: D1.3, R1.2
unnamed: D1.4, U1.18
unnamed: D1.6, U1.17
unnamed: D2.2, U1.16
unnamed: D2.3, R2.2
unnamed: D2.4, U1.15
unnamed: D2.6, U1.14
unnamed: D3.2, U1.13
unnamed: D3.3, R3.2
unnamed: D3.4, U1.12
unnamed: D3.6, U4.19
unnamed: D4.2, U4.18
unnamed: D4.3, R4.2
unnamed: D4.4, U4.17
unnamed: D4.6, U4.16
unnamed: D5.2, U4.15
unnamed: D5.3, R5.2
unnamed: D5.4, U4.14
unnamed: D5.6, U4.13
unnamed: D6.1, U4.12
unnamed: D6.2, R6.2
unnamed: JP1.2, U2.6
unnamed: L1.1, U2.4
unnamed: L1.2, U2.2

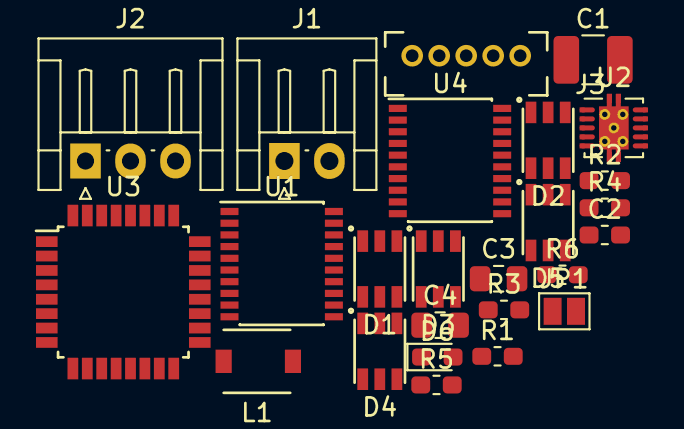
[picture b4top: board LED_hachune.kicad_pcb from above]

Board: 2 copper layers, 25 parts (0 on the bottom side), 45 nets, no tracks yet.
